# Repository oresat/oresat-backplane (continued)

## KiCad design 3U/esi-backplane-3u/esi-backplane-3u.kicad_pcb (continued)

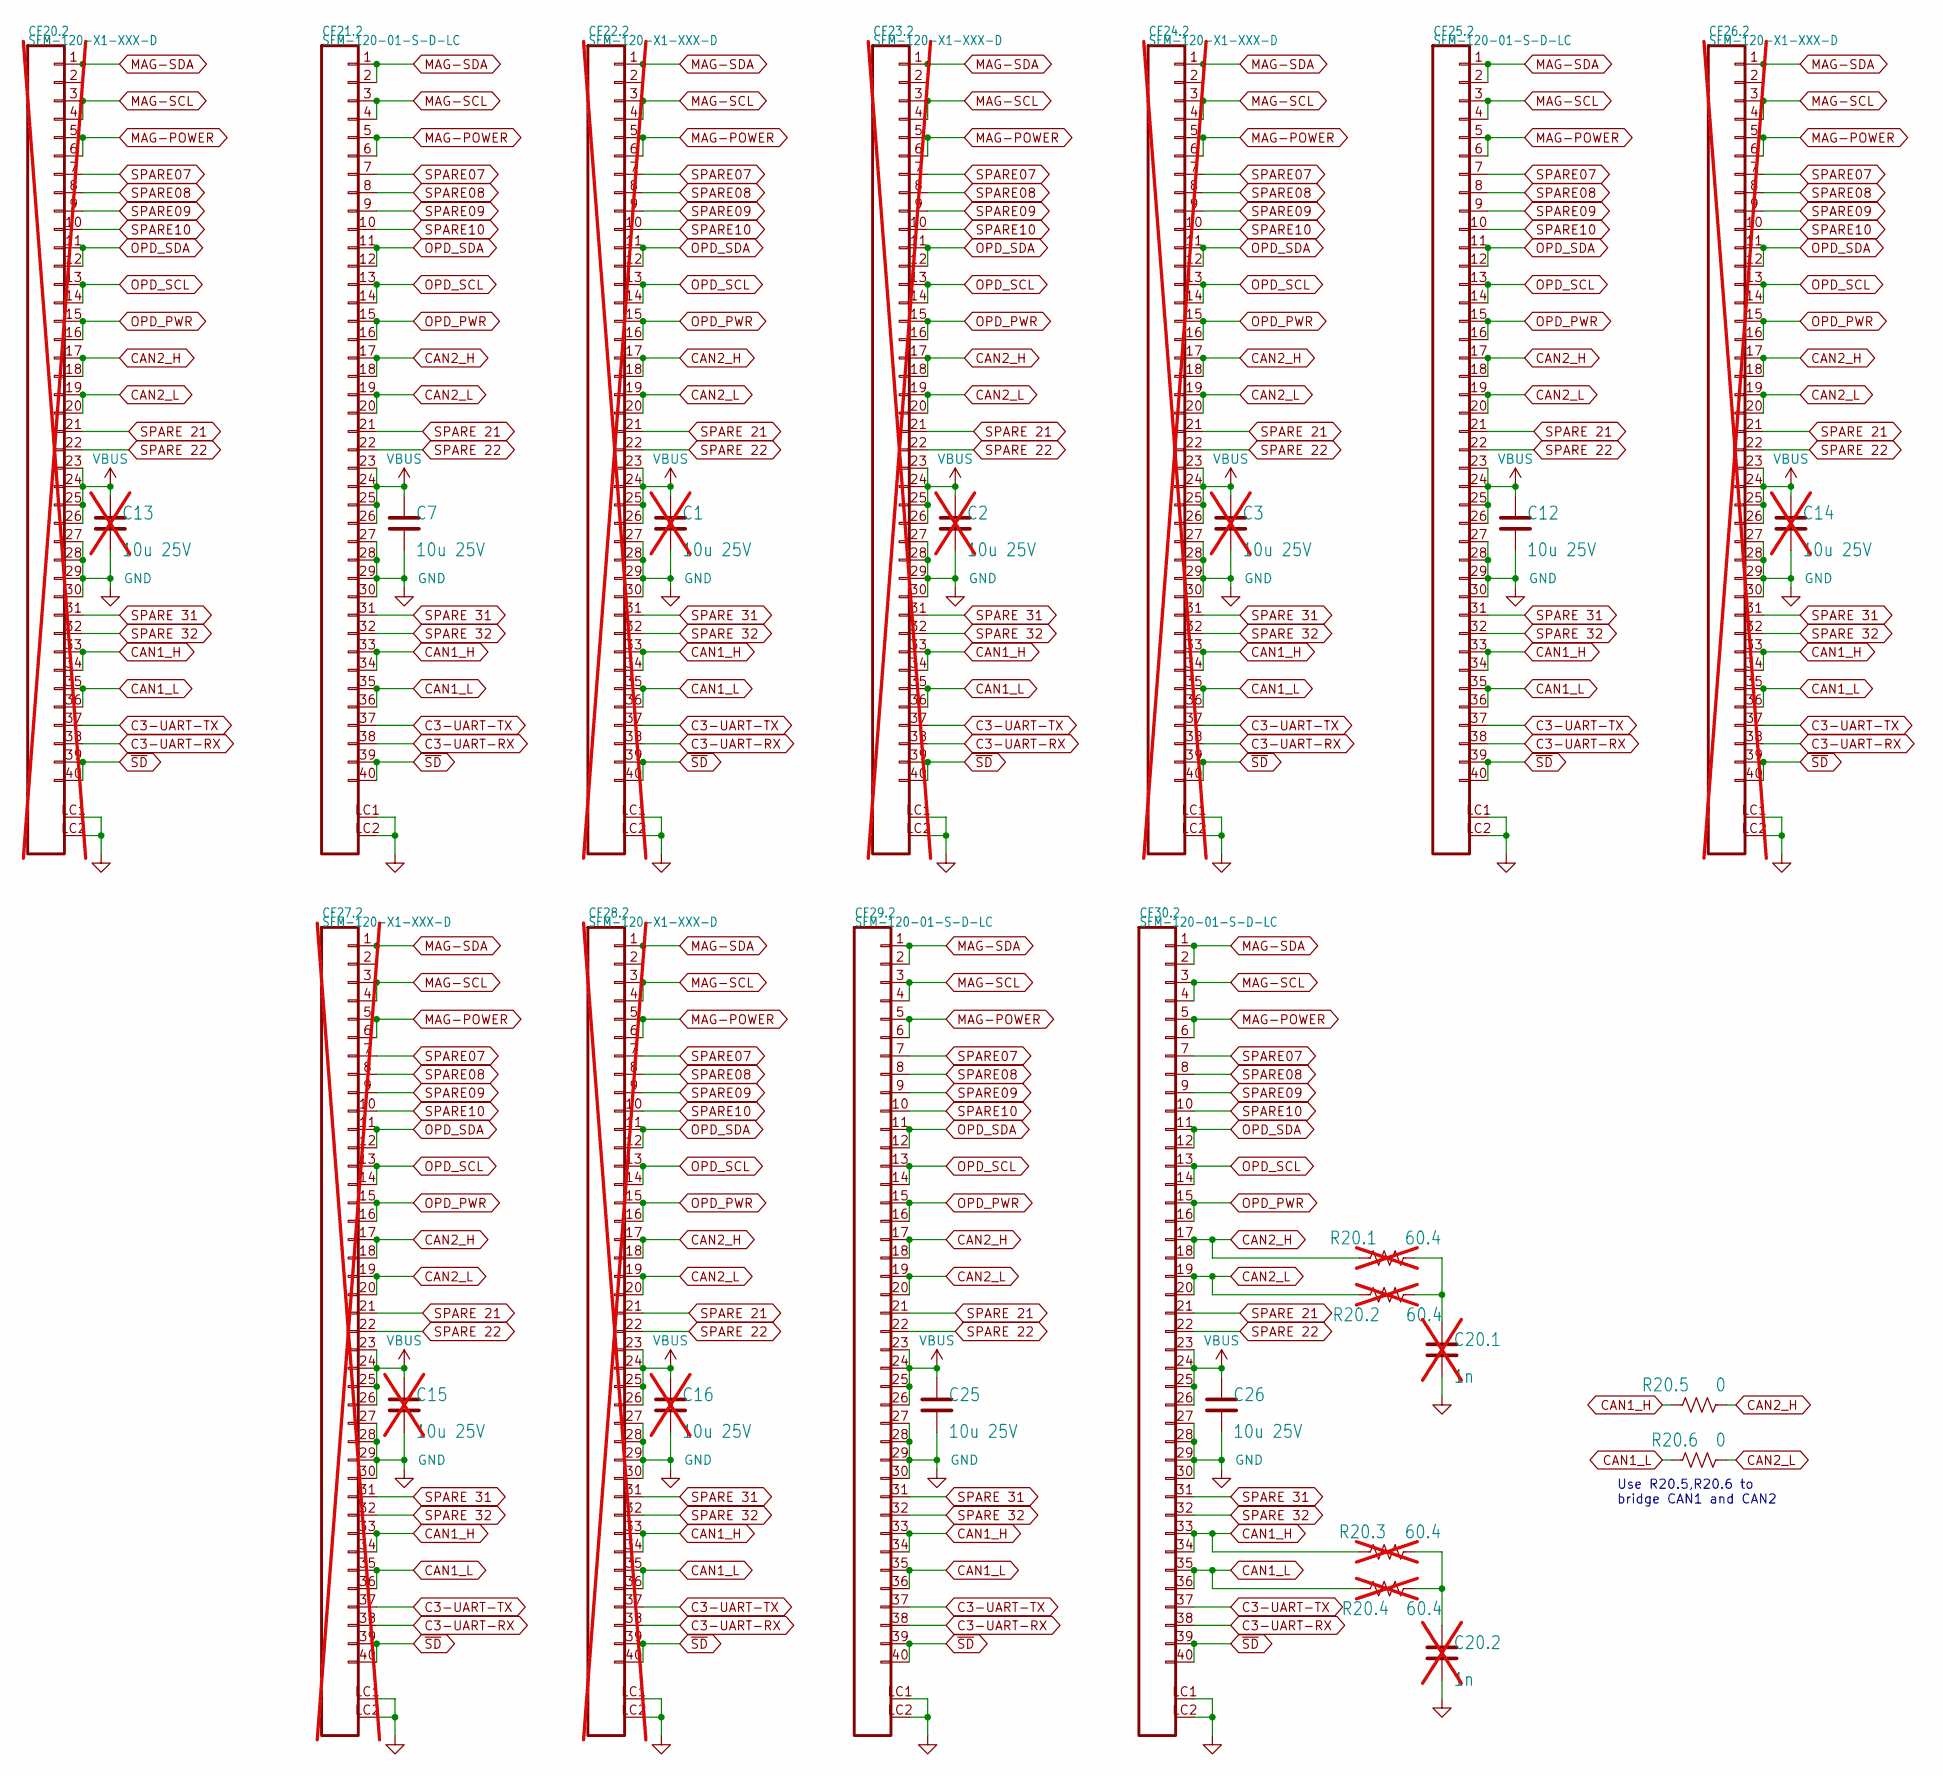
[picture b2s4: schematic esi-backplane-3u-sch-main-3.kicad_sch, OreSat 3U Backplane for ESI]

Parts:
C1, C2, C3, C13, C14, C15, C16: 10u 25V; C_1206_3216Metric; MPN TMK316AB7106KLHT; not fitted
C7, C12, C25, C26: 10u 25V; C_1206_3216Metric; MPN TMK316AB7106KLHT
C20.1, C20.2: 1n; 0603-C-NOSILK; MPN C0603C102J5GECAUTO; not fitted
CF20.2, CF22.2, CF23.2, CF24.2, CF26.2, CF27.2, CF28.2: SFM-120-X1-XXX-D; J-SAMTEC-SFM-120-X1-XXX-D; MPN SFM-120-01-S-D-LC; not fitted
CF21.2, CF25.2, CF29.2, CF30.2: SFM-120-01-S-D-LC; J-SAMTEC-SFM-120-X1-XXX-D; MPN SFM-120-01-S-D-LC
R20.1, R20.2, R20.3, R20.4: 60.4; R_1206_3216Metric; MPN RMCF1206FT60R4; not fitted
R20.5, R20.6: 0; 0603-C-NOSILK; MPN RMCF0603ZT0R00

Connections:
C3-UART-RX: CF20.2.38, CF21.2.38, CF22.2.38, CF23.2.38, CF24.2.38, CF25.2.38, CF26.2.38, CF27.2.38, CF28.2.38, CF29.2.38, CF30.2.38; also elsewhere on the board
C3-UART-TX: CF20.2.37, CF21.2.37, CF22.2.37, CF23.2.37, CF24.2.37, CF25.2.37, CF26.2.37, CF27.2.37, CF28.2.37, CF29.2.37, CF30.2.37; also elsewhere on the board
CAN1_H: CF20.2.33, CF20.2.34, CF21.2.33, CF21.2.34, CF22.2.33, CF22.2.34, CF23.2.33, CF23.2.34, CF24.2.33, CF24.2.34, CF25.2.33, CF25.2.34, CF26.2.33, CF26.2.34, CF27.2.33, CF27.2.34, CF28.2.33, CF28.2.34, CF29.2.33, CF29.2.34, CF30.2.33, CF30.2.34, R20.3.1, R20.5.1; also elsewhere on the board
CAN1_L: CF20.2.35, CF20.2.36, CF21.2.35, CF21.2.36, CF22.2.35, CF22.2.36, CF23.2.35, CF23.2.36, CF24.2.35, CF24.2.36, CF25.2.35, CF25.2.36, CF26.2.35, CF26.2.36, CF27.2.35, CF27.2.36, CF28.2.35, CF28.2.36, CF29.2.35, CF29.2.36, CF30.2.35, CF30.2.36, R20.4.2, R20.6.1; also elsewhere on the board
CAN2_H: CF20.2.17, CF20.2.18, CF21.2.17, CF21.2.18, CF22.2.17, CF22.2.18, CF23.2.17, CF23.2.18, CF24.2.17, CF24.2.18, CF25.2.17, CF25.2.18, CF26.2.17, CF26.2.18, CF27.2.17, CF27.2.18, CF28.2.17, CF28.2.18, CF29.2.17, CF29.2.18, CF30.2.17, CF30.2.18, R20.1.1, R20.5.2; also elsewhere on the board
CAN2_L: CF20.2.19, CF20.2.20, CF21.2.19, CF21.2.20, CF22.2.19, CF22.2.20, CF23.2.19, CF23.2.20, CF24.2.19, CF24.2.20, CF25.2.19, CF25.2.20, CF26.2.19, CF26.2.20, CF27.2.19, CF27.2.20, CF28.2.19, CF28.2.20, CF29.2.19, CF29.2.20, CF30.2.19, CF30.2.20, R20.2.2, R20.6.2; also elsewhere on the board
GND: C1.2, C2.2, C3.2, C7.2, C12.2, C13.2, C14.2, C15.2, C16.2, C20.1.2, C20.2.2, C25.2, C26.2, CF20.2.27, CF20.2.28, CF20.2.29, CF20.2.30, CF20.2.LC1, CF20.2.LC2, CF21.2.27, CF21.2.28, CF21.2.29, CF21.2.30, CF21.2.LC1, CF21.2.LC2, CF22.2.27, CF22.2.28, CF22.2.29, CF22.2.30, CF22.2.LC1, CF22.2.LC2, CF23.2.27, CF23.2.28, CF23.2.29, CF23.2.30, CF23.2.LC1, CF23.2.LC2, CF24.2.27, CF24.2.28, CF24.2.29, CF24.2.30, CF24.2.LC1, CF24.2.LC2, CF25.2.27, CF25.2.28, CF25.2.29, CF25.2.30, CF25.2.LC1, CF25.2.LC2, CF26.2.27, CF26.2.28, CF26.2.29, CF26.2.30, CF26.2.LC1, CF26.2.LC2, CF27.2.27, CF27.2.28, CF27.2.29, CF27.2.30, CF27.2.LC1, CF27.2.LC2, CF28.2.27, CF28.2.28, CF28.2.29, CF28.2.30, CF28.2.LC1, CF28.2.LC2, CF29.2.27, CF29.2.28, CF29.2.29, CF29.2.30, CF29.2.LC1, CF29.2.LC2, CF30.2.27, CF30.2.28, CF30.2.29, CF30.2.30, CF30.2.LC1, CF30.2.LC2; also elsewhere on the board
MAG-POWER: CF20.2.5, CF20.2.6, CF21.2.5, CF21.2.6, CF22.2.5, CF22.2.6, CF23.2.5, CF23.2.6, CF24.2.5, CF24.2.6, CF25.2.5, CF25.2.6, CF26.2.5, CF26.2.6, CF27.2.5, CF27.2.6, CF28.2.5, CF28.2.6, CF29.2.5, CF29.2.6, CF30.2.5, CF30.2.6; also elsewhere on the board
MAG-SCL: CF20.2.3, CF20.2.4, CF21.2.3, CF21.2.4, CF22.2.3, CF22.2.4, CF23.2.3, CF23.2.4, CF24.2.3, CF24.2.4, CF25.2.3, CF25.2.4, CF26.2.3, CF26.2.4, CF27.2.3, CF27.2.4, CF28.2.3, CF28.2.4, CF29.2.3, CF29.2.4, CF30.2.3, CF30.2.4; also elsewhere on the board
MAG-SDA: CF20.2.1, CF20.2.2, CF21.2.1, CF21.2.2, CF22.2.1, CF22.2.2, CF23.2.1, CF23.2.2, CF24.2.1, CF24.2.2, CF25.2.1, CF25.2.2, CF26.2.1, CF26.2.2, CF27.2.1, CF27.2.2, CF28.2.1, CF28.2.2, CF29.2.1, CF29.2.2, CF30.2.1, CF30.2.2; also elsewhere on the board
unnamed: C20.1.1, R20.1.2, R20.2.1
unnamed: C20.2.1, R20.3.2, R20.4.1
OPD_PWR: CF20.2.15, CF20.2.16, CF21.2.15, CF21.2.16, CF22.2.15, CF22.2.16, CF23.2.15, CF23.2.16, CF24.2.15, CF24.2.16, CF25.2.15, CF25.2.16, CF26.2.15, CF26.2.16, CF27.2.15, CF27.2.16, CF28.2.15, CF28.2.16, CF29.2.15, CF29.2.16, CF30.2.15, CF30.2.16; also elsewhere on the board
OPD_SCL: CF20.2.13, CF20.2.14, CF21.2.13, CF21.2.14, CF22.2.13, CF22.2.14, CF23.2.13, CF23.2.14, CF24.2.13, CF24.2.14, CF25.2.13, CF25.2.14, CF26.2.13, CF26.2.14, CF27.2.13, CF27.2.14, CF28.2.13, CF28.2.14, CF29.2.13, CF29.2.14, CF30.2.13, CF30.2.14; also elsewhere on the board
OPD_SDA: CF20.2.11, CF20.2.12, CF21.2.11, CF21.2.12, CF22.2.11, CF22.2.12, CF23.2.11, CF23.2.12, CF24.2.11, CF24.2.12, CF25.2.11, CF25.2.12, CF26.2.11, CF26.2.12, CF27.2.11, CF27.2.12, CF28.2.11, CF28.2.12, CF29.2.11, CF29.2.12, CF30.2.11, CF30.2.12; also elsewhere on the board
SPARE07: CF20.2.7, CF21.2.7, CF22.2.7, CF23.2.7, CF24.2.7, CF25.2.7, CF26.2.7, CF27.2.7, CF28.2.7, CF29.2.7, CF30.2.7; also elsewhere on the board
SPARE08: CF20.2.8, CF21.2.8, CF22.2.8, CF23.2.8, CF24.2.8, CF25.2.8, CF26.2.8, CF27.2.8, CF28.2.8, CF29.2.8, CF30.2.8; also elsewhere on the board
SPARE09: CF20.2.9, CF21.2.9, CF22.2.9, CF23.2.9, CF24.2.9, CF25.2.9, CF26.2.9, CF27.2.9, CF28.2.9, CF29.2.9, CF30.2.9; also elsewhere on the board
SPARE10: CF20.2.10, CF21.2.10, CF22.2.10, CF23.2.10, CF24.2.10, CF25.2.10, CF26.2.10, CF27.2.10, CF28.2.10, CF29.2.10, CF30.2.10; also elsewhere on the board
SPARE 21: CF20.2.21, CF21.2.21, CF22.2.21, CF23.2.21, CF24.2.21, CF25.2.21, CF26.2.21, CF27.2.21, CF28.2.21, CF29.2.21, CF30.2.21; also elsewhere on the board
SPARE 22: CF20.2.22, CF21.2.22, CF22.2.22, CF23.2.22, CF24.2.22, CF25.2.22, CF26.2.22, CF27.2.22, CF28.2.22, CF29.2.22, CF30.2.22; also elsewhere on the board
SPARE 31: CF20.2.31, CF21.2.31, CF22.2.31, CF23.2.31, CF24.2.31, CF25.2.31, CF26.2.31, CF27.2.31, CF28.2.31, CF29.2.31, CF30.2.31; also elsewhere on the board
SPARE 32: CF20.2.32, CF21.2.32, CF22.2.32, CF23.2.32, CF24.2.32, CF25.2.32, CF26.2.32, CF27.2.32, CF28.2.32, CF29.2.32, CF30.2.32; also elsewhere on the board
VBUS: C1.1, C2.1, C3.1, C7.1, C12.1, C13.1, C14.1, C15.1, C16.1, C25.1, C26.1, CF20.2.23, CF20.2.24, CF20.2.25, CF20.2.26, CF21.2.23, CF21.2.24, CF21.2.25, CF21.2.26, CF22.2.23, CF22.2.24, CF22.2.25, CF22.2.26, CF23.2.23, CF23.2.24, CF23.2.25, CF23.2.26, CF24.2.23, CF24.2.24, CF24.2.25, CF24.2.26, CF25.2.23, CF25.2.24, CF25.2.25, CF25.2.26, CF26.2.23, CF26.2.24, CF26.2.25, CF26.2.26, CF27.2.23, CF27.2.24, CF27.2.25, CF27.2.26, CF28.2.23, CF28.2.24, CF28.2.25, CF28.2.26, CF29.2.23, CF29.2.24, CF29.2.25, CF29.2.26, CF30.2.23, CF30.2.24, CF30.2.25, CF30.2.26; also elsewhere on the board
~SD: CF20.2.39, CF20.2.40, CF21.2.39, CF21.2.40, CF22.2.39, CF22.2.40, CF23.2.39, CF23.2.40, CF24.2.39, CF24.2.40, CF25.2.39, CF25.2.40, CF26.2.39, CF26.2.40, CF27.2.39, CF27.2.40, CF28.2.39, CF28.2.40, CF29.2.39, CF29.2.40, CF30.2.39, CF30.2.40; also elsewhere on the board

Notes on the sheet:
Use R20.5,R20.6 to bridge CAN1 and CAN2

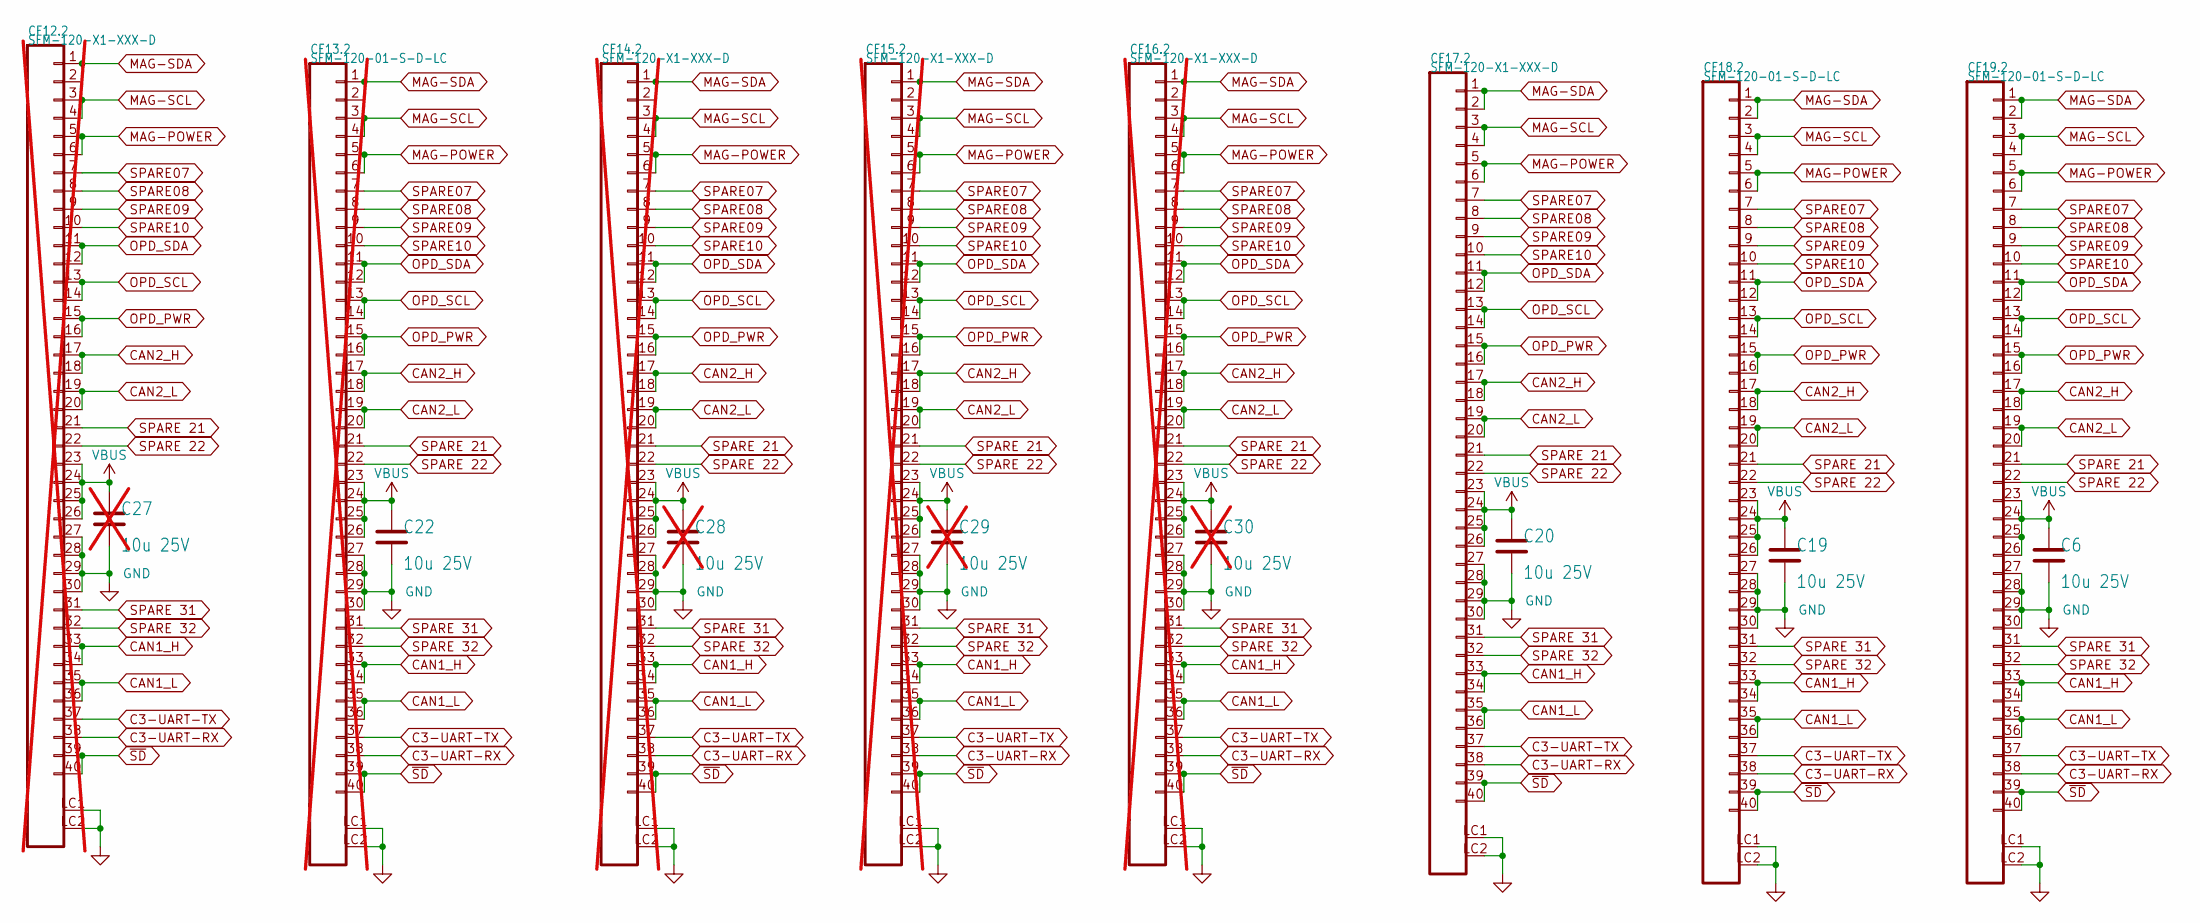
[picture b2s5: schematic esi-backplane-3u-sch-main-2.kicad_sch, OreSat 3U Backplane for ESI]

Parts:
C6, C19, C20, C22: 10u 25V; C_1206_3216Metric; MPN TMK316AB7106KLHT
C27, C28, C29, C30: 10u 25V; C_1206_3216Metric; MPN TMK316AB7106KLHT; not fitted
CF12.2, CF14.2, CF15.2, CF16.2: SFM-120-X1-XXX-D; J-SAMTEC-SFM-120-X1-XXX-D; MPN SFM-120-01-S-D-LC; not fitted
CF13.2: SFM-120-01-S-D-LC; J-SAMTEC-SFM-120-X1-XXX-D; MPN SFM-120-01-S-D-LC; not fitted
CF17.2: SFM-120-X1-XXX-D; J-SAMTEC-SFM-120-X1-XXX-D; MPN SFM-120-01-S-D-LC
CF18.2, CF19.2: SFM-120-01-S-D-LC; J-SAMTEC-SFM-120-X1-XXX-D; MPN SFM-120-01-S-D-LC

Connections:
C3-UART-RX: CF12.2.38, CF13.2.38, CF14.2.38, CF15.2.38, CF16.2.38, CF17.2.38, CF18.2.38, CF19.2.38; also elsewhere on the board
C3-UART-TX: CF12.2.37, CF13.2.37, CF14.2.37, CF15.2.37, CF16.2.37, CF17.2.37, CF18.2.37, CF19.2.37; also elsewhere on the board
CAN1_H: CF12.2.33, CF12.2.34, CF13.2.33, CF13.2.34, CF14.2.33, CF14.2.34, CF15.2.33, CF15.2.34, CF16.2.33, CF16.2.34, CF17.2.33, CF17.2.34, CF18.2.33, CF18.2.34, CF19.2.33, CF19.2.34; also elsewhere on the board
CAN1_L: CF12.2.35, CF12.2.36, CF13.2.35, CF13.2.36, CF14.2.35, CF14.2.36, CF15.2.35, CF15.2.36, CF16.2.35, CF16.2.36, CF17.2.35, CF17.2.36, CF18.2.35, CF18.2.36, CF19.2.35, CF19.2.36; also elsewhere on the board
CAN2_H: CF12.2.17, CF12.2.18, CF13.2.17, CF13.2.18, CF14.2.17, CF14.2.18, CF15.2.17, CF15.2.18, CF16.2.17, CF16.2.18, CF17.2.17, CF17.2.18, CF18.2.17, CF18.2.18, CF19.2.17, CF19.2.18; also elsewhere on the board
CAN2_L: CF12.2.19, CF12.2.20, CF13.2.19, CF13.2.20, CF14.2.19, CF14.2.20, CF15.2.19, CF15.2.20, CF16.2.19, CF16.2.20, CF17.2.19, CF17.2.20, CF18.2.19, CF18.2.20, CF19.2.19, CF19.2.20; also elsewhere on the board
GND: C6.2, C19.2, C20.2, C22.2, C27.2, C28.2, C29.2, C30.2, CF12.2.27, CF12.2.28, CF12.2.29, CF12.2.30, CF12.2.LC1, CF12.2.LC2, CF13.2.27, CF13.2.28, CF13.2.29, CF13.2.30, CF13.2.LC1, CF13.2.LC2, CF14.2.27, CF14.2.28, CF14.2.29, CF14.2.30, CF14.2.LC1, CF14.2.LC2, CF15.2.27, CF15.2.28, CF15.2.29, CF15.2.30, CF15.2.LC1, CF15.2.LC2, CF16.2.27, CF16.2.28, CF16.2.29, CF16.2.30, CF16.2.LC1, CF16.2.LC2, CF17.2.27, CF17.2.28, CF17.2.29, CF17.2.30, CF17.2.LC1, CF17.2.LC2, CF18.2.27, CF18.2.28, CF18.2.29, CF18.2.30, CF18.2.LC1, CF18.2.LC2, CF19.2.27, CF19.2.28, CF19.2.29, CF19.2.30, CF19.2.LC1, CF19.2.LC2; also elsewhere on the board
MAG-POWER: CF12.2.5, CF12.2.6, CF13.2.5, CF13.2.6, CF14.2.5, CF14.2.6, CF15.2.5, CF15.2.6, CF16.2.5, CF16.2.6, CF17.2.5, CF17.2.6, CF18.2.5, CF18.2.6, CF19.2.5, CF19.2.6; also elsewhere on the board
MAG-SCL: CF12.2.3, CF12.2.4, CF13.2.3, CF13.2.4, CF14.2.3, CF14.2.4, CF15.2.3, CF15.2.4, CF16.2.3, CF16.2.4, CF17.2.3, CF17.2.4, CF18.2.3, CF18.2.4, CF19.2.3, CF19.2.4; also elsewhere on the board
MAG-SDA: CF12.2.1, CF12.2.2, CF13.2.1, CF13.2.2, CF14.2.1, CF14.2.2, CF15.2.1, CF15.2.2, CF16.2.1, CF16.2.2, CF17.2.1, CF17.2.2, CF18.2.1, CF18.2.2, CF19.2.1, CF19.2.2; also elsewhere on the board
OPD_PWR: CF12.2.15, CF12.2.16, CF13.2.15, CF13.2.16, CF14.2.15, CF14.2.16, CF15.2.15, CF15.2.16, CF16.2.15, CF16.2.16, CF17.2.15, CF17.2.16, CF18.2.15, CF18.2.16, CF19.2.15, CF19.2.16; also elsewhere on the board
OPD_SCL: CF12.2.13, CF12.2.14, CF13.2.13, CF13.2.14, CF14.2.13, CF14.2.14, CF15.2.13, CF15.2.14, CF16.2.13, CF16.2.14, CF17.2.13, CF17.2.14, CF18.2.13, CF18.2.14, CF19.2.13, CF19.2.14; also elsewhere on the board
OPD_SDA: CF12.2.11, CF12.2.12, CF13.2.11, CF13.2.12, CF14.2.11, CF14.2.12, CF15.2.11, CF15.2.12, CF16.2.11, CF16.2.12, CF17.2.11, CF17.2.12, CF18.2.11, CF18.2.12, CF19.2.11, CF19.2.12; also elsewhere on the board
SPARE07: CF12.2.7, CF13.2.7, CF14.2.7, CF15.2.7, CF16.2.7, CF17.2.7, CF18.2.7, CF19.2.7; also elsewhere on the board
SPARE08: CF12.2.8, CF13.2.8, CF14.2.8, CF15.2.8, CF16.2.8, CF17.2.8, CF18.2.8, CF19.2.8; also elsewhere on the board
SPARE09: CF12.2.9, CF13.2.9, CF14.2.9, CF15.2.9, CF16.2.9, CF17.2.9, CF18.2.9, CF19.2.9; also elsewhere on the board
SPARE10: CF12.2.10, CF13.2.10, CF14.2.10, CF15.2.10, CF16.2.10, CF17.2.10, CF18.2.10, CF19.2.10; also elsewhere on the board
SPARE 21: CF12.2.21, CF13.2.21, CF14.2.21, CF15.2.21, CF16.2.21, CF17.2.21, CF18.2.21, CF19.2.21; also elsewhere on the board
SPARE 22: CF12.2.22, CF13.2.22, CF14.2.22, CF15.2.22, CF16.2.22, CF17.2.22, CF18.2.22, CF19.2.22; also elsewhere on the board
SPARE 31: CF12.2.31, CF13.2.31, CF14.2.31, CF15.2.31, CF16.2.31, CF17.2.31, CF18.2.31, CF19.2.31; also elsewhere on the board
SPARE 32: CF12.2.32, CF13.2.32, CF14.2.32, CF15.2.32, CF16.2.32, CF17.2.32, CF18.2.32, CF19.2.32; also elsewhere on the board
VBUS: C6.1, C19.1, C20.1, C22.1, C27.1, C28.1, C29.1, C30.1, CF12.2.23, CF12.2.24, CF12.2.25, CF12.2.26, CF13.2.23, CF13.2.24, CF13.2.25, CF13.2.26, CF14.2.23, CF14.2.24, CF14.2.25, CF14.2.26, CF15.2.23, CF15.2.24, CF15.2.25, CF15.2.26, CF16.2.23, CF16.2.24, CF16.2.25, CF16.2.26, CF17.2.23, CF17.2.24, CF17.2.25, CF17.2.26, CF18.2.23, CF18.2.24, CF18.2.25, CF18.2.26, CF19.2.23, CF19.2.24, CF19.2.25, CF19.2.26; also elsewhere on the board
~SD: CF12.2.39, CF12.2.40, CF13.2.39, CF13.2.40, CF14.2.39, CF14.2.40, CF15.2.39, CF15.2.40, CF16.2.39, CF16.2.40, CF17.2.39, CF17.2.40, CF18.2.39, CF18.2.40, CF19.2.39, CF19.2.40; also elsewhere on the board

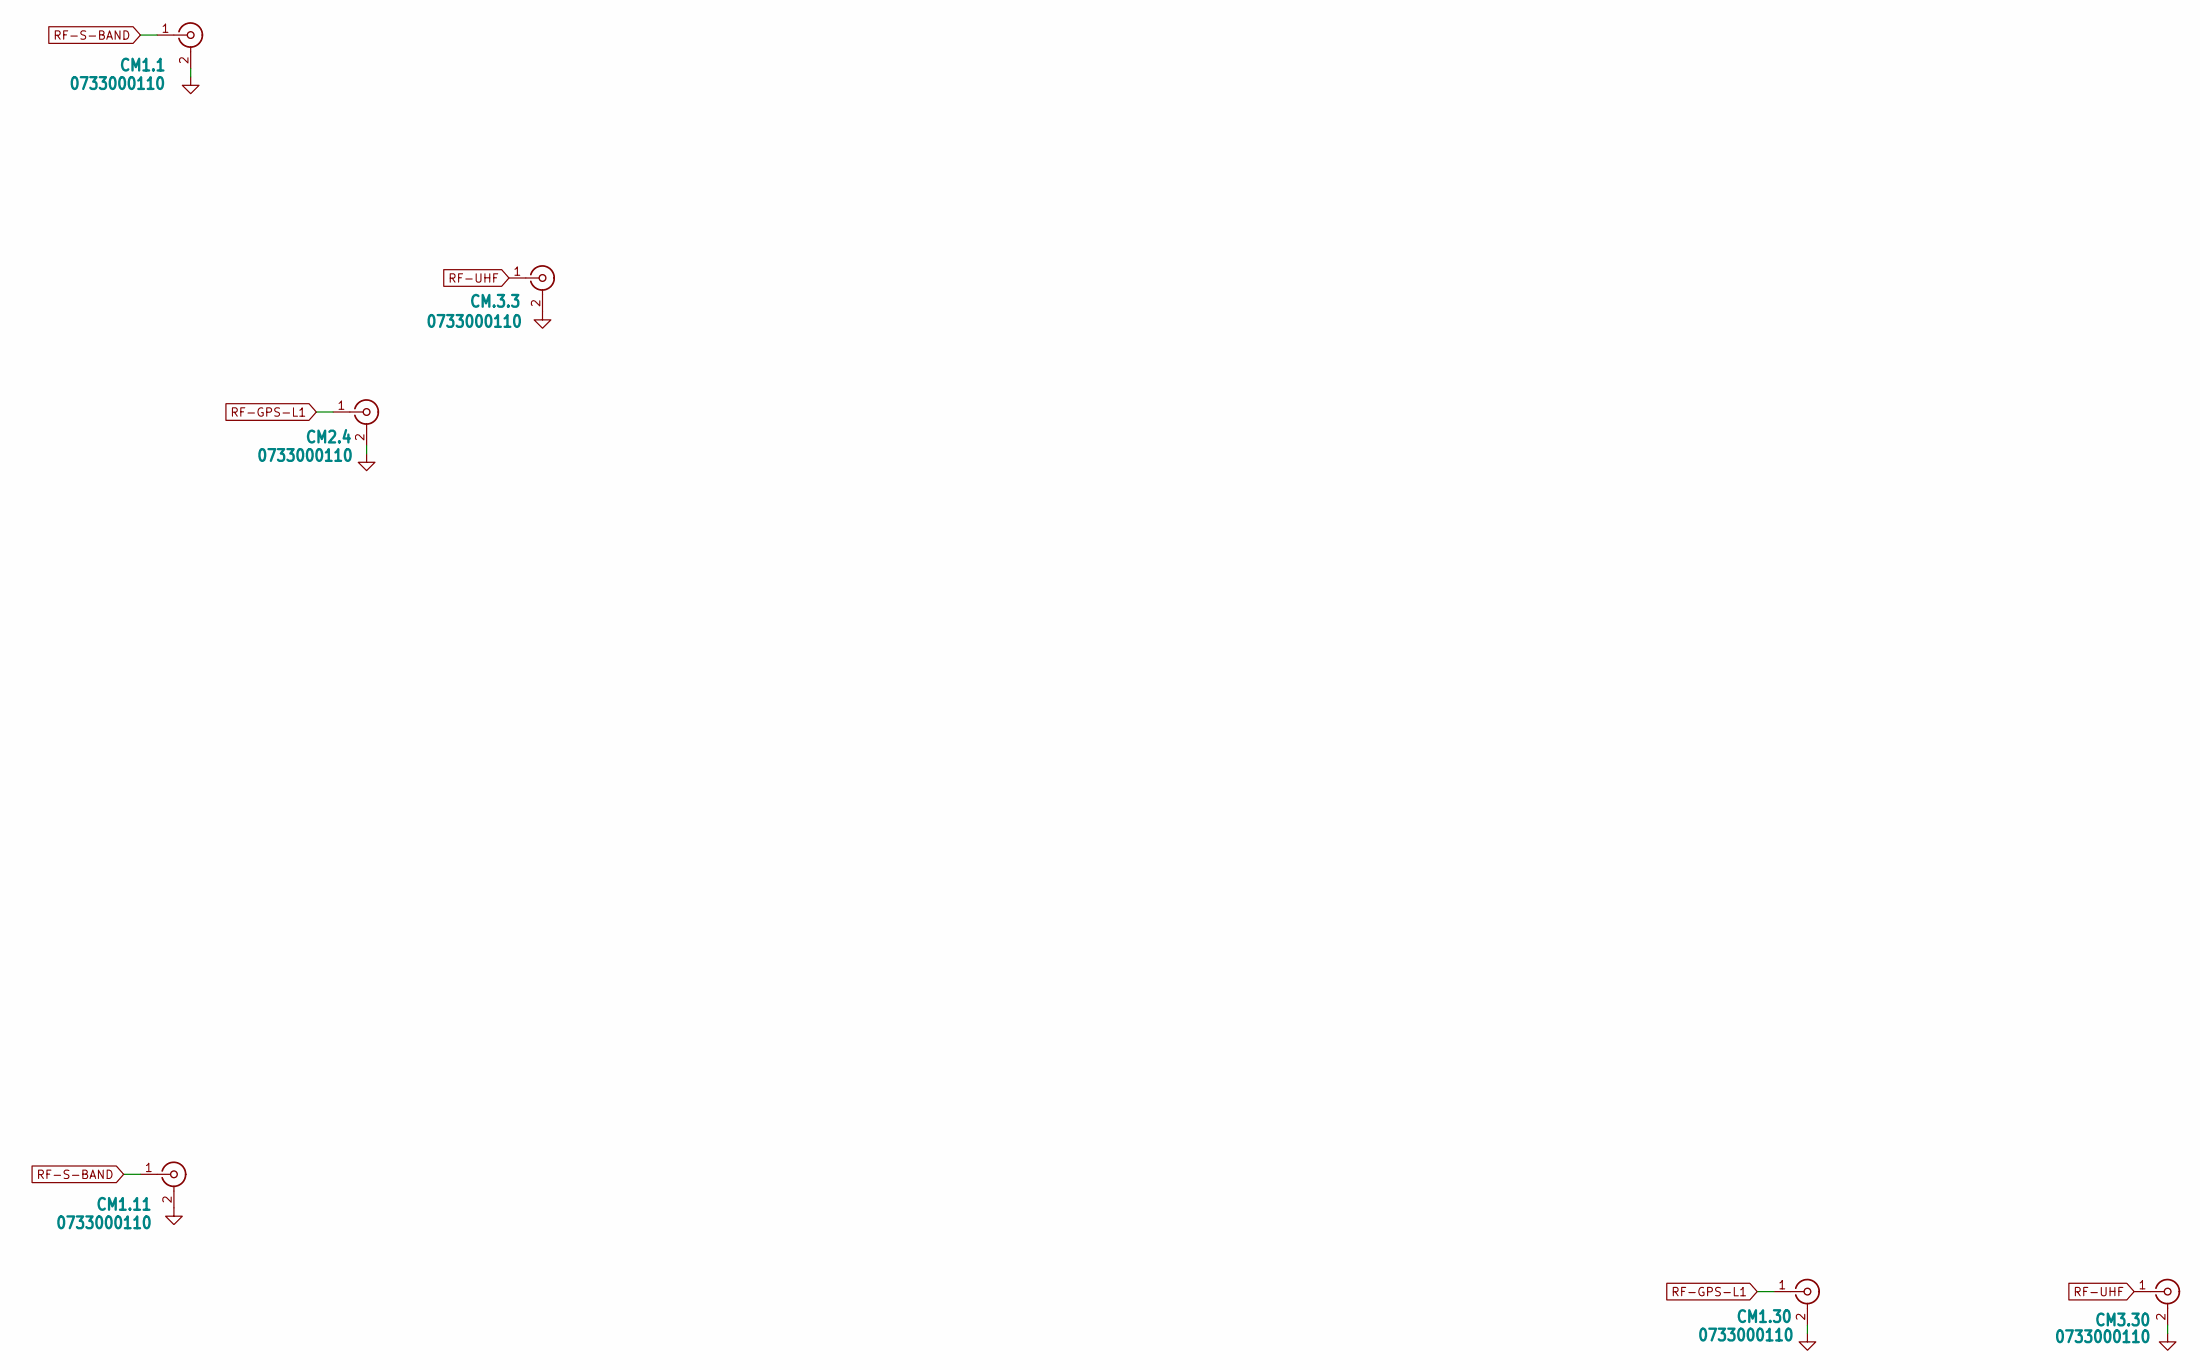
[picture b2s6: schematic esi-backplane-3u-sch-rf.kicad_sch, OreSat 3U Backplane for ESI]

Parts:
CM1.1, CM1.11, CM1.30, CM2.4, CM3.30, CM.3.3: 0733000110; J-MOLEX-SMPM-73300-011X; MPN 0733000110

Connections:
GND: CM1.1.2 (Ext), CM1.11.2 (Ext), CM1.30.2 (Ext), CM2.4.2 (Ext), CM3.30.2 (Ext), CM.3.3.2 (Ext); also elsewhere on the board
RF-GPS-L1: CM1.30.1 (In), CM2.4.1 (In)
RF-S-BAND: CM1.1.1 (In), CM1.11.1 (In)
RF-UHF: CM3.30.1 (In), CM.3.3.1 (In)

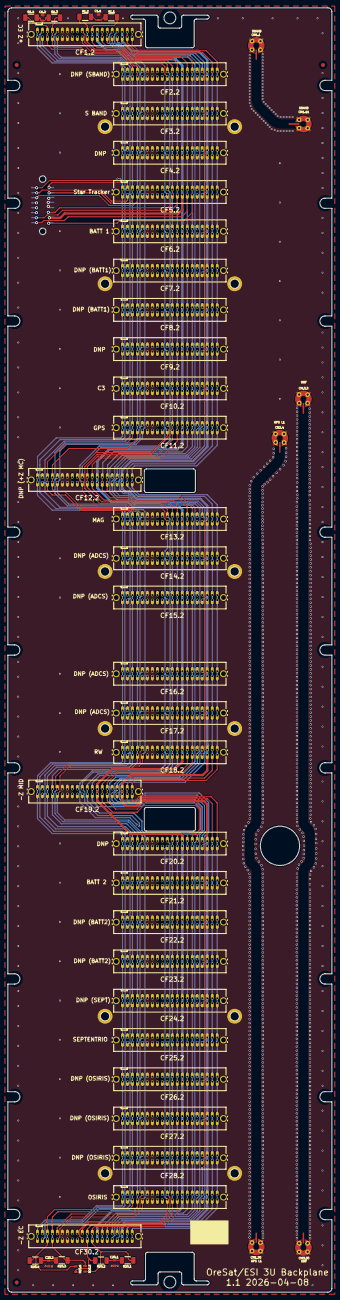
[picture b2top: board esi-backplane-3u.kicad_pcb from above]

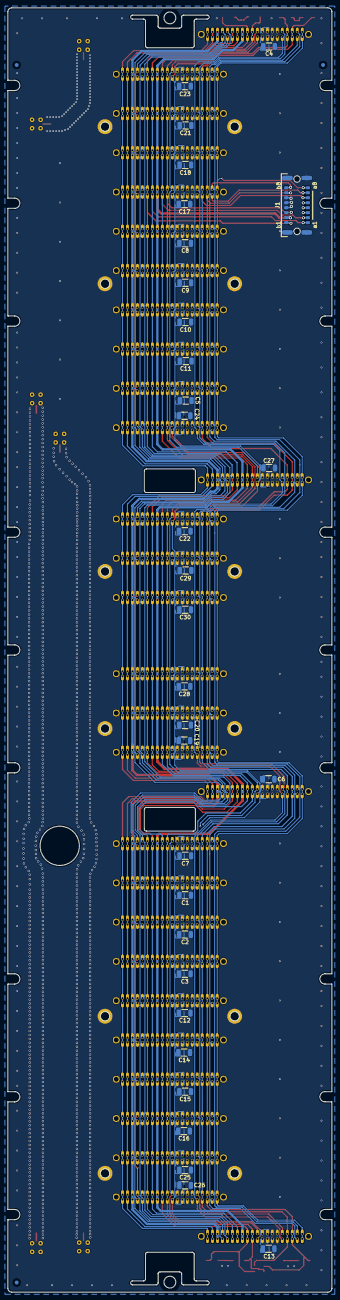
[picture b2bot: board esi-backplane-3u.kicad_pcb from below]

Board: 4 copper layers, 82.5 x 327.0 mm, 101 parts (34 on the bottom side), 30 nets.

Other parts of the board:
PH1, PH2: MountingHole_3mm
